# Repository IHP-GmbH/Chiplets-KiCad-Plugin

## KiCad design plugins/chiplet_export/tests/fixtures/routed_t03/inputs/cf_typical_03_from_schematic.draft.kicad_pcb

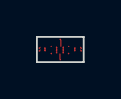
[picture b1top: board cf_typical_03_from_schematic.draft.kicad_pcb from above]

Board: 4 copper layers, 2.6 x 1.4 mm, 8 parts (0 on the bottom side), 10 nets.

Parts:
J1, J2, J3, J4, J5, J6: EXT_PAD; EXT_PAD_80um
U1: PAD_FRAME_L
U2: PAD_FRAME_R

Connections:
unnamed: J1.1, U1.ext[0]
unnamed: J2.1, U1.ext[1]
unnamed: J3.1, U2.ext[0]
unnamed: J4.1, U2.ext[1]
VDD: J5.1, U1.VDD, U2.VDD
VSS: J6.1, U1.VSS, U2.VSS
lane0: U1.d2d[0], U2.d2d[0]
lane1: U1.d2d[1], U2.d2d[1]
lane2: U1.d2d[2], U2.d2d[2]
lane3: U1.d2d[3], U2.d2d[3]
